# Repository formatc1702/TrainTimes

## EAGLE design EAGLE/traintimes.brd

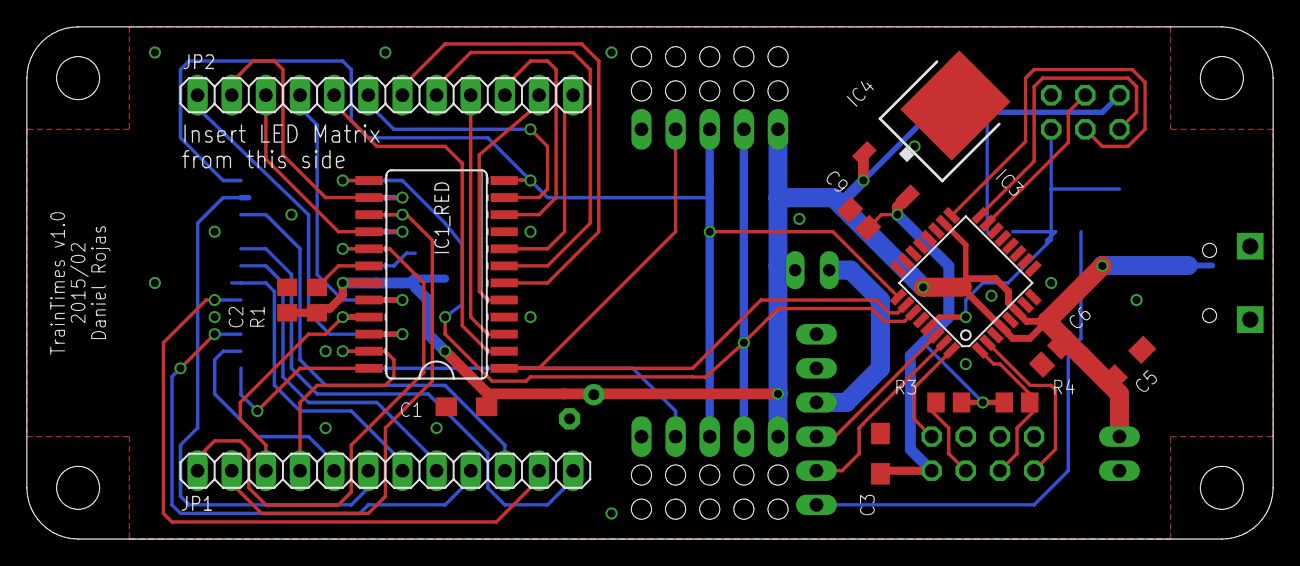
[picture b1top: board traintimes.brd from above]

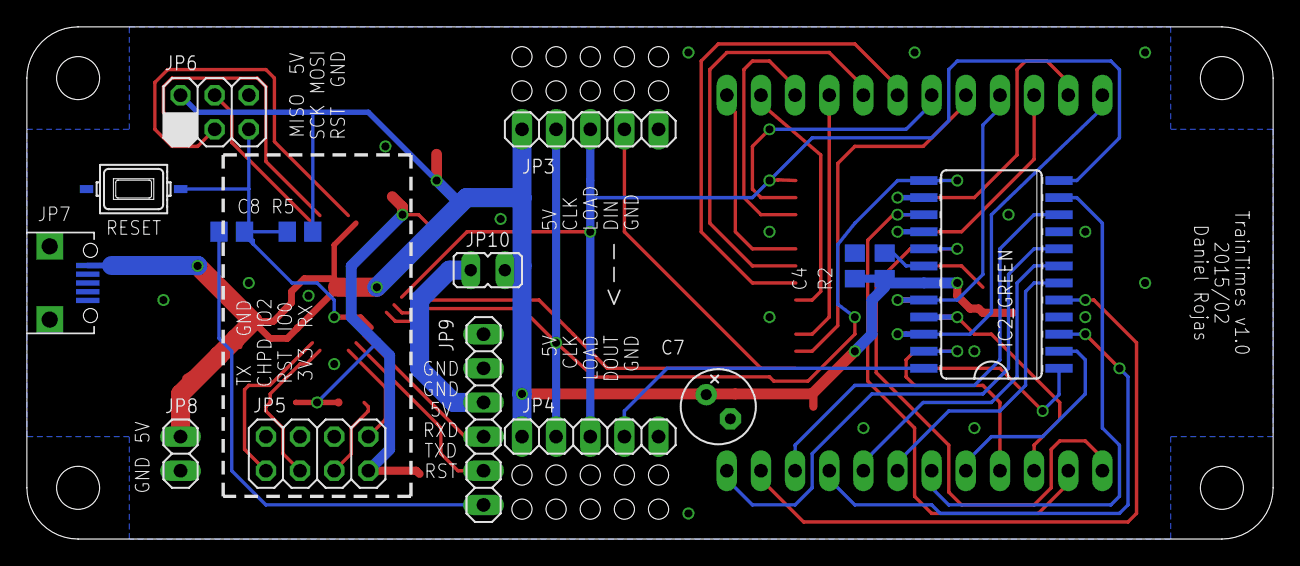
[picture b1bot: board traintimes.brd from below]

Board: 2 copper layers, 92.7 x 38.1 mm, 29 parts (15 on the bottom side), 46 nets.

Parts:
C1, C3, C5: 1uF; SMC_A
C2, C4, C6, C8, C9: 100nF; C0805
C7: 22uF; E2,5-6
IC1_RED, IC2_GREEN: MAX7221CWG; SO24L
IC3: ATMEGA328P; TQFP32-08
IC4: TS2940CP33; TO252
JP1: LED_PIN_1-12; 1X12
JP2: LED_PIN_24-13; 1X12
JP3: BUS_IN; 1X05
JP4: BUS_OUT; 1X05
JP5: ESP-01; 2X04
JP6: ICSP; 2X03
JP7: USB; FCI-10103594-0001LF
JP8: POWER; 1X02
JP9: FTDI; 1X06
JP10: FTDI_5V_EN; JP1
R1, R2: 3k3; R0805
R3, R4, R5: 10k; R0805
SW1: RESET; SW_TACT_3X6

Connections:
+3V3: C3.+, C9.1, IC4.2, JP5.2, R3.2, R4.2
+5V: C1.+, C2.1, C4.1, C5.+, C6.1, C7.+, IC1_RED.19, IC2_GREEN.19, IC3.4, IC3.6, IC3.18, IC4.1, JP3.1, JP4.1, JP6.2, JP7.1, JP8.1, JP10.2, R1.1, R2.1, R5.2
CLK: IC1_RED.13, IC2_GREEN.13, IC3.27, JP3.2, JP4.2
DINDOUT_INT: IC1_RED.24, IC2_GREEN.1
DIN_EXT: IC1_RED.1, IC3.26, JP3.4
DOUT_EXT: IC2_GREEN.24, JP4.4
ESP_CHPD: IC3.1, JP5.6, R4.1
ESP_RST: JP5.4, R3.1
ESP_RX: IC3.32, JP5.1
ESP_TX: IC3.2, JP5.8
GND: C1.-, C2.2, C3.-, C4.2, C5.-, C6.2, C7.-, C9.2, IC1_RED.4, IC1_RED.9, IC2_GREEN.4, IC2_GREEN.9, IC3.3, IC3.5, IC3.21, IC4.3, JP3.5, JP4.5, JP5.7, JP6.6, JP7.5, JP8.2, JP9.5, JP9.6, SW1.2
GRN0: IC2_GREEN.2, JP1.5
GRN1: IC2_GREEN.11, JP1.6
GRN2: IC2_GREEN.6, JP1.7
GRN3: IC2_GREEN.7, JP1.8
GRN4: IC2_GREEN.3, JP1.9
GRN5: IC2_GREEN.10, JP1.10
GRN6: IC2_GREEN.5, JP1.11
GRN7: IC2_GREEN.8, JP1.12
ISET1: IC1_RED.18, R1.2
ISET2: IC2_GREEN.18, R2.2
LOAD: IC1_RED.12, IC2_GREEN.12, IC3.25, JP3.3, JP4.3
MEGA_RST: C8.2, IC3.29, JP6.5, R5.1, SW1.1
MISO: IC3.16, JP6.1
MOSI: IC3.15, JP6.4
RED0: IC1_RED.2, JP2.8
RED1: IC1_RED.11, JP2.7
RED2: IC1_RED.6, JP2.6
RED3: IC1_RED.7, JP2.5
RED4: IC1_RED.3, JP2.4
RED5: IC1_RED.10, JP2.3
RED6: IC1_RED.5, JP2.2
RED7: IC1_RED.8, JP2.1
ROW0_DP: IC1_RED.22, IC2_GREEN.22, JP2.12
ROW1_A: IC1_RED.14, IC2_GREEN.14, JP2.11
ROW2_B: IC1_RED.16, IC2_GREEN.16, JP2.10
ROW3_C: IC1_RED.20, IC2_GREEN.20, JP2.9
ROW4_D: IC1_RED.23, IC2_GREEN.23, JP1.4
ROW5_E: IC1_RED.21, IC2_GREEN.21, JP1.3
ROW6_F: IC1_RED.15, IC2_GREEN.15, JP1.2
ROW7_G: IC1_RED.17, IC2_GREEN.17, JP1.1
SCK: IC3.17, JP6.3
UART_DTR: C8.1, JP9.1
UART_RX: IC3.30, JP9.3
UART_TX: IC3.31, JP9.2
UART_VCC: JP9.4, JP10.1

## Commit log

2016-10-15 Add .gitignore
2016-10-15 Add EAGLE files
2016-10-15 Add Inkscape files
2016-10-15 Edit .gitignore
2016-10-15 Add Arduino code
2016-10-15 Add Lua code for ESP8266
2016-10-15 Update Lua (2016-02-18)
2016-10-15 Update Lua code
2016-10-15 Add EAGLE .gitignore
2016-10-15 Add PHP crawler
2016-10-15 Prepared usersettings.lua file
    SSID / Key / Server URL settings will be stored here.
    Functionality to actually read this file not yet implemented!
2016-10-23 White on dark
2016-10-23 Fix lines
2016-10-23 Prepare for printing
2016-10-23 Add output PDF
2016-10-27 Make characters 1px smaller on top, shift 1px to left
2016-10-27 Make characters rounder, 4 prettier
2016-10-27 Add comments in displaychars.h
2016-11-05 Reorder Inkscape design files
2016-11-26 Minimum working example (HTTP GET)
    Caution! Add \n to end of every line for esplorer to uplaod correctly
    \\r\\n OK? Not sure...
2016-11-26 Basic parse test working (matching)
2016-11-26 Extracting the correct lines work, now need to compare the times
2016-11-26 MicroPython Socket ReadLine working
2016-11-26 Not quite... syntax error line 54
2016-11-26 At least now the error is fixed
    Use print() function instead of print statement
2016-11-26 Woohoo! Works!
    Missing: Get server time, calculate time until departures, format for arduino, clean up etc
2016-11-26 Add wificonfig.txt for SSID+password
2016-11-26 Less printing
2016-11-26 Added main.py to avoid error message...
2016-11-27 Move code to bvg.py, add NTP service, rudimentary time difference calculation
2016-11-27 Split up long lines
2016-11-27 Some trouble uploading files, code should be fine though
2016-11-27 Remove \n's
2016-11-27 Working again using mpfshell
2016-11-27 Some last minute stuff
2016-11-27 Move code to main.py for autoexec
2016-11-27 Add status blinks
2016-11-27 Comment out display test at startup (all LEDs on)
2016-11-27 Reduce WiFi UART timeout
2016-11-27 Add TODO
2016-11-27 Try forcing display to update ASAP, still not working...
2016-11-27 Remove negative numbers from results (untested)
2016-11-27 Move tests to subfolder and .gitignore them
2017-02-08 Add sleep mode (UNTESTED!)
2017-02-10 Add rotating ‘loading’ screen
2017-02-10 Remove some debugging output
2017-02-10 Implement CHPD (ESP-01) / RST (NodeMCU) pin functionality
2017-02-10 Add small changes
2017-02-10 Add PlatformIO project folder
2017-02-10 Add libraries
2017-02-10 Working code (loading animation only)
2017-02-10 Working code (StateMachine with scrolling)
2017-02-10 Semi-working code (Train Time parsing works, display frames are not updated)
2017-02-10 Working code (instant display receive, auto-sleep)
2017-02-10 Archive old Arduino firmware and Lua script (replaced by MicroPython)
2017-02-13 Filter out results < 60s (including 0, which breaks Arduino’s ParseInt)
2017-02-13 Wait until WiFi connected (40s timeout) before requesting data
2017-02-13 Small improvements, remove debug mode
2017-02-13 Add walking time feature to each station
2017-02-13 Add MPF subfolder
2017-02-15 Archive PHP parser
2017-02-17 Disable WebREPL on boot
2017-02-17 Add delay on ESP8266 TX side and loosen UART timeout on Arduino RX side to reduce problems
2017-02-17 Implement ESP8266 deep sleep after successful transmission (or sure failure)
2017-03-29 Add missing destinations
2017-03-29 Add quick hack for CEST (summer time)
2017-04-27 Implement minimum working example with VBB API
2017-04-27 Attempt to reduce memory usage -> not working
2017-04-28 Use urequest class to simplify code
2017-04-28 Add NTP and utime features
2017-04-28 Clean up data structure
2017-04-28 Further clean up
2017-04-28 Store Station IDs in text file, format output for Arduino
2017-04-28 Add comments
2017-04-28 More clean up
2017-04-29 Add dirty webserver proof of concept
2017-04-29 Clean up server proof of concept, read/write SSID+PW works
2017-09-14 Update station IDs (but not working, waiting for reply from VBB API team)
2017-09-14 Add some more debugging
2017-09-14 Make departure station names unambiguous for (new?) API?
2017-09-14 Enable debugging (temporary)
2017-09-22 Account for possibility of getting 0 results for a given connection
2017-09-22 Actualy print to UART
2017-09-22 Add small buffer between transmissions of each direction to allow Arduino to read its buffer
2017-09-22 Make debugging output optional
2017-09-22 Add walking time for each station to remove departures that are too earlt
2017-09-22 Implement ESP deepsleep after transmit
2017-11-03 Change server URL to VBB production server
2017-11-03 Summer time has ended.
2017-11-03 Change debugging output a bit
2017-11-21 Create some fake data for the FabContest
2018-04-03 Revert "Summer time has ended."
    This reverts commit 3bb42d2795b9464ed7cda3b8c78a28bc55e3fa24.
2018-04-04 Change Display #7 to new workplace
2020-12-06 Add switch to select CET/CEST
2021-10-02 Update VBB API URL
2021-10-02 Add optional printing of VBB API response
2021-10-02 Rename directories, update .gitignore
2021-10-02 Add instructions to apikey.template.txt
2021-10-02 Restructure MicroPython firmware directory
2021-10-02 Improve upload script
2021-10-02 Add installation instructions
    so far, only for MicroPython ESP firmware
2021-10-02 Restore display #7 to line 21 to Lichtenberg
2021-10-02 Add serial output monitoring instructions
2021-10-08 Implement `debug()` [intermediate commit]
2021-10-08 Continue implementing `debug()` [intermediate commit]
2021-10-08 Finish implementing `debug()`
2021-10-08 Change all strings from double quote to single quote
2021-10-08 Adapt to ESP-32 board
2021-10-08 Replace instances of `.format()` with f-strings
2021-10-08 Update UART pins for ESP32
2021-10-08 Add selective upload script
